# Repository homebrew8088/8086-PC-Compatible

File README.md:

# 8086 PC Compatible

This is a repository for my 8086 PC Compatible project developed in 2021. The Motherboard is built to be generally PC XT/AT compatible.\
\
THIS DOES NOT WORK CORRECTLY FOR REFERENCE ONLY  

https://www.homebrew8088.com \
http://www.ebay.com/sch/emil6190/m.html

**Features:**\
-8086, NEC V30\
-512k RAM (This can be changed)\
-16 Bit ISA Slots\
-PC Speaker\
-USB "Hard Drive"\
-PS/2 Keyboard\
-ATX form factor\
-Add on DMA controller (Has not been built) 

This project is very closely related to my other 8088 PC Compatible project https://github.com/homebrew8088/8088-PC-Compatible

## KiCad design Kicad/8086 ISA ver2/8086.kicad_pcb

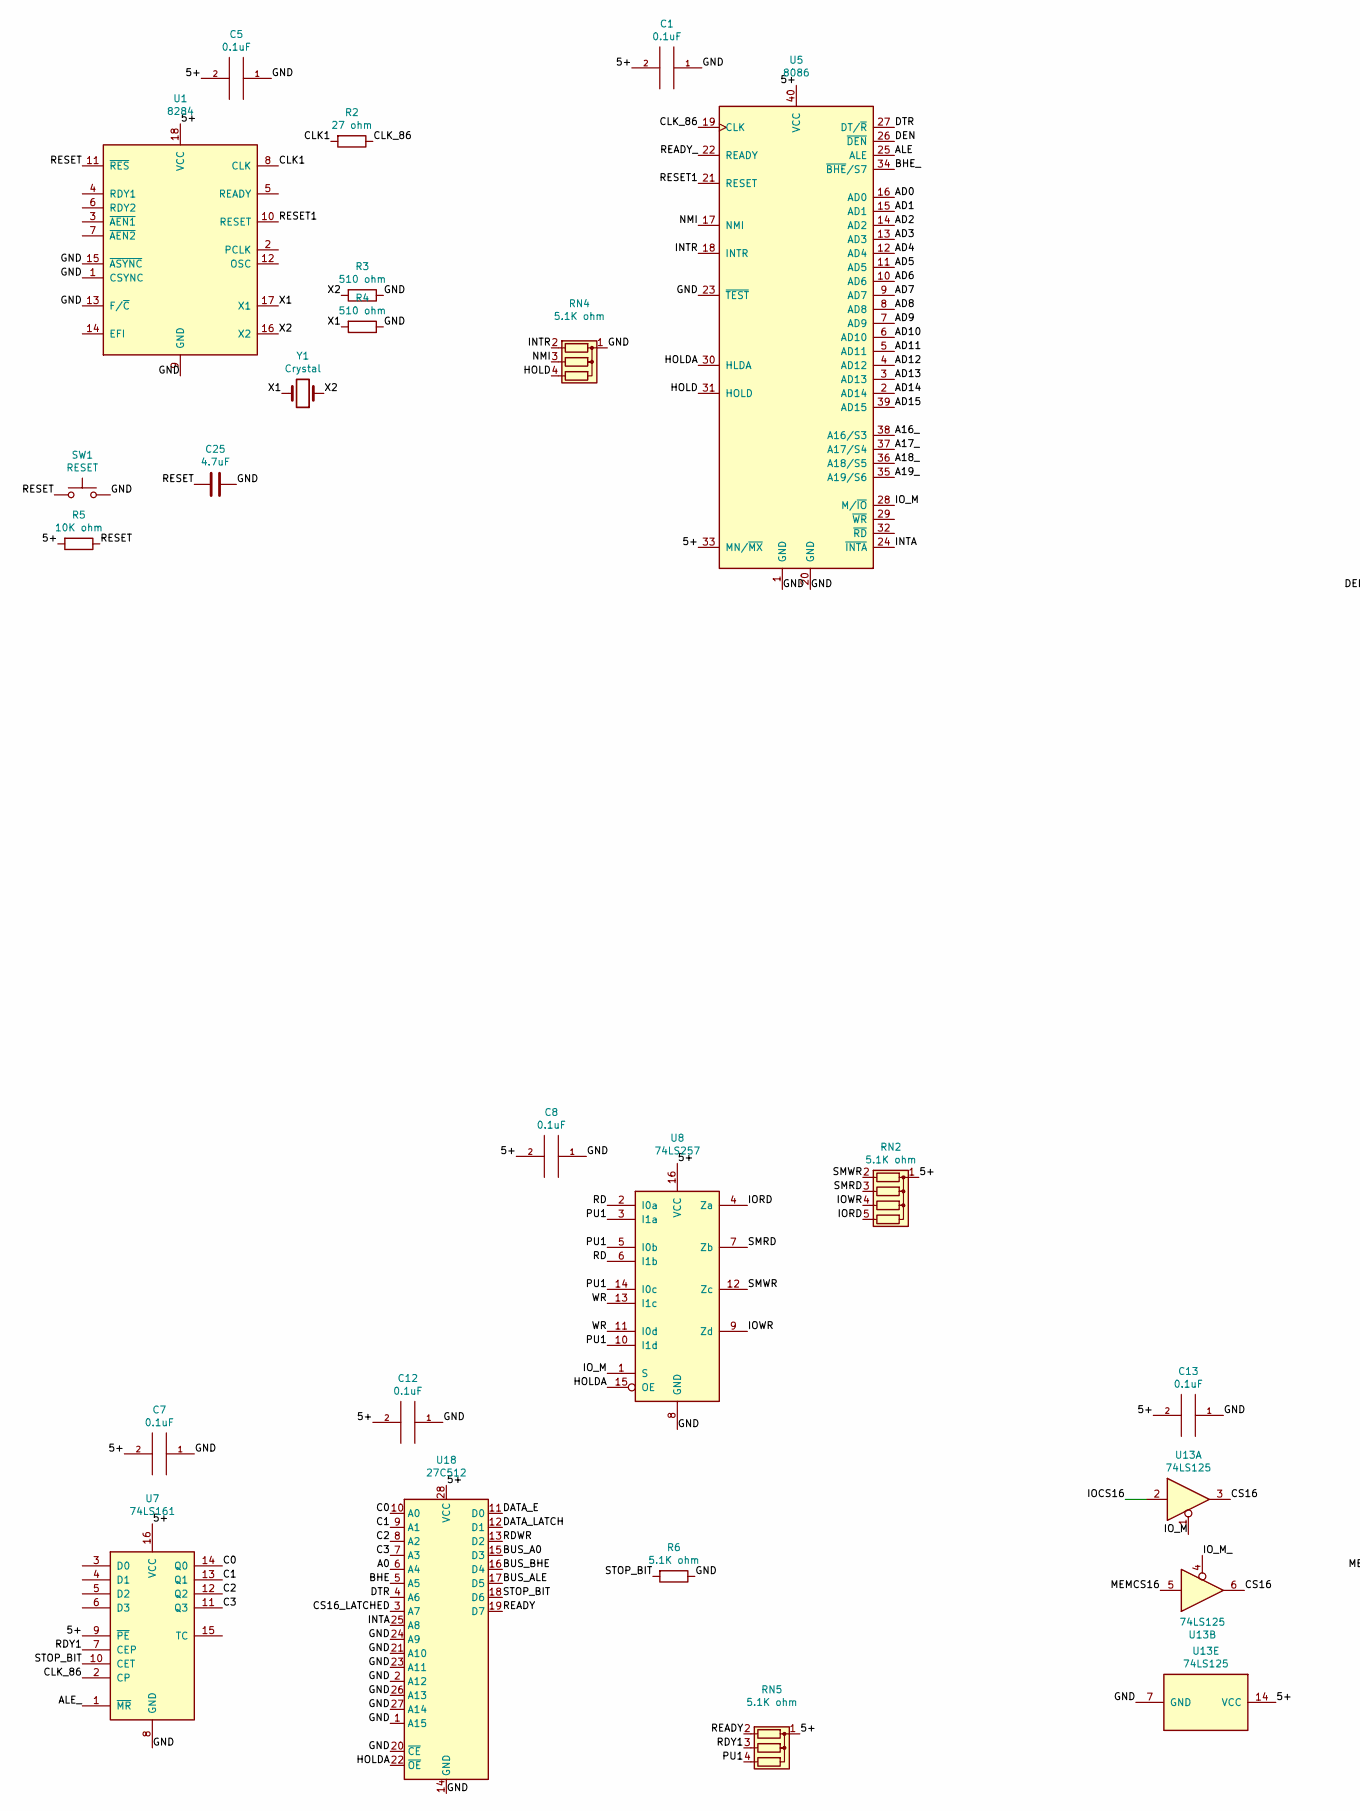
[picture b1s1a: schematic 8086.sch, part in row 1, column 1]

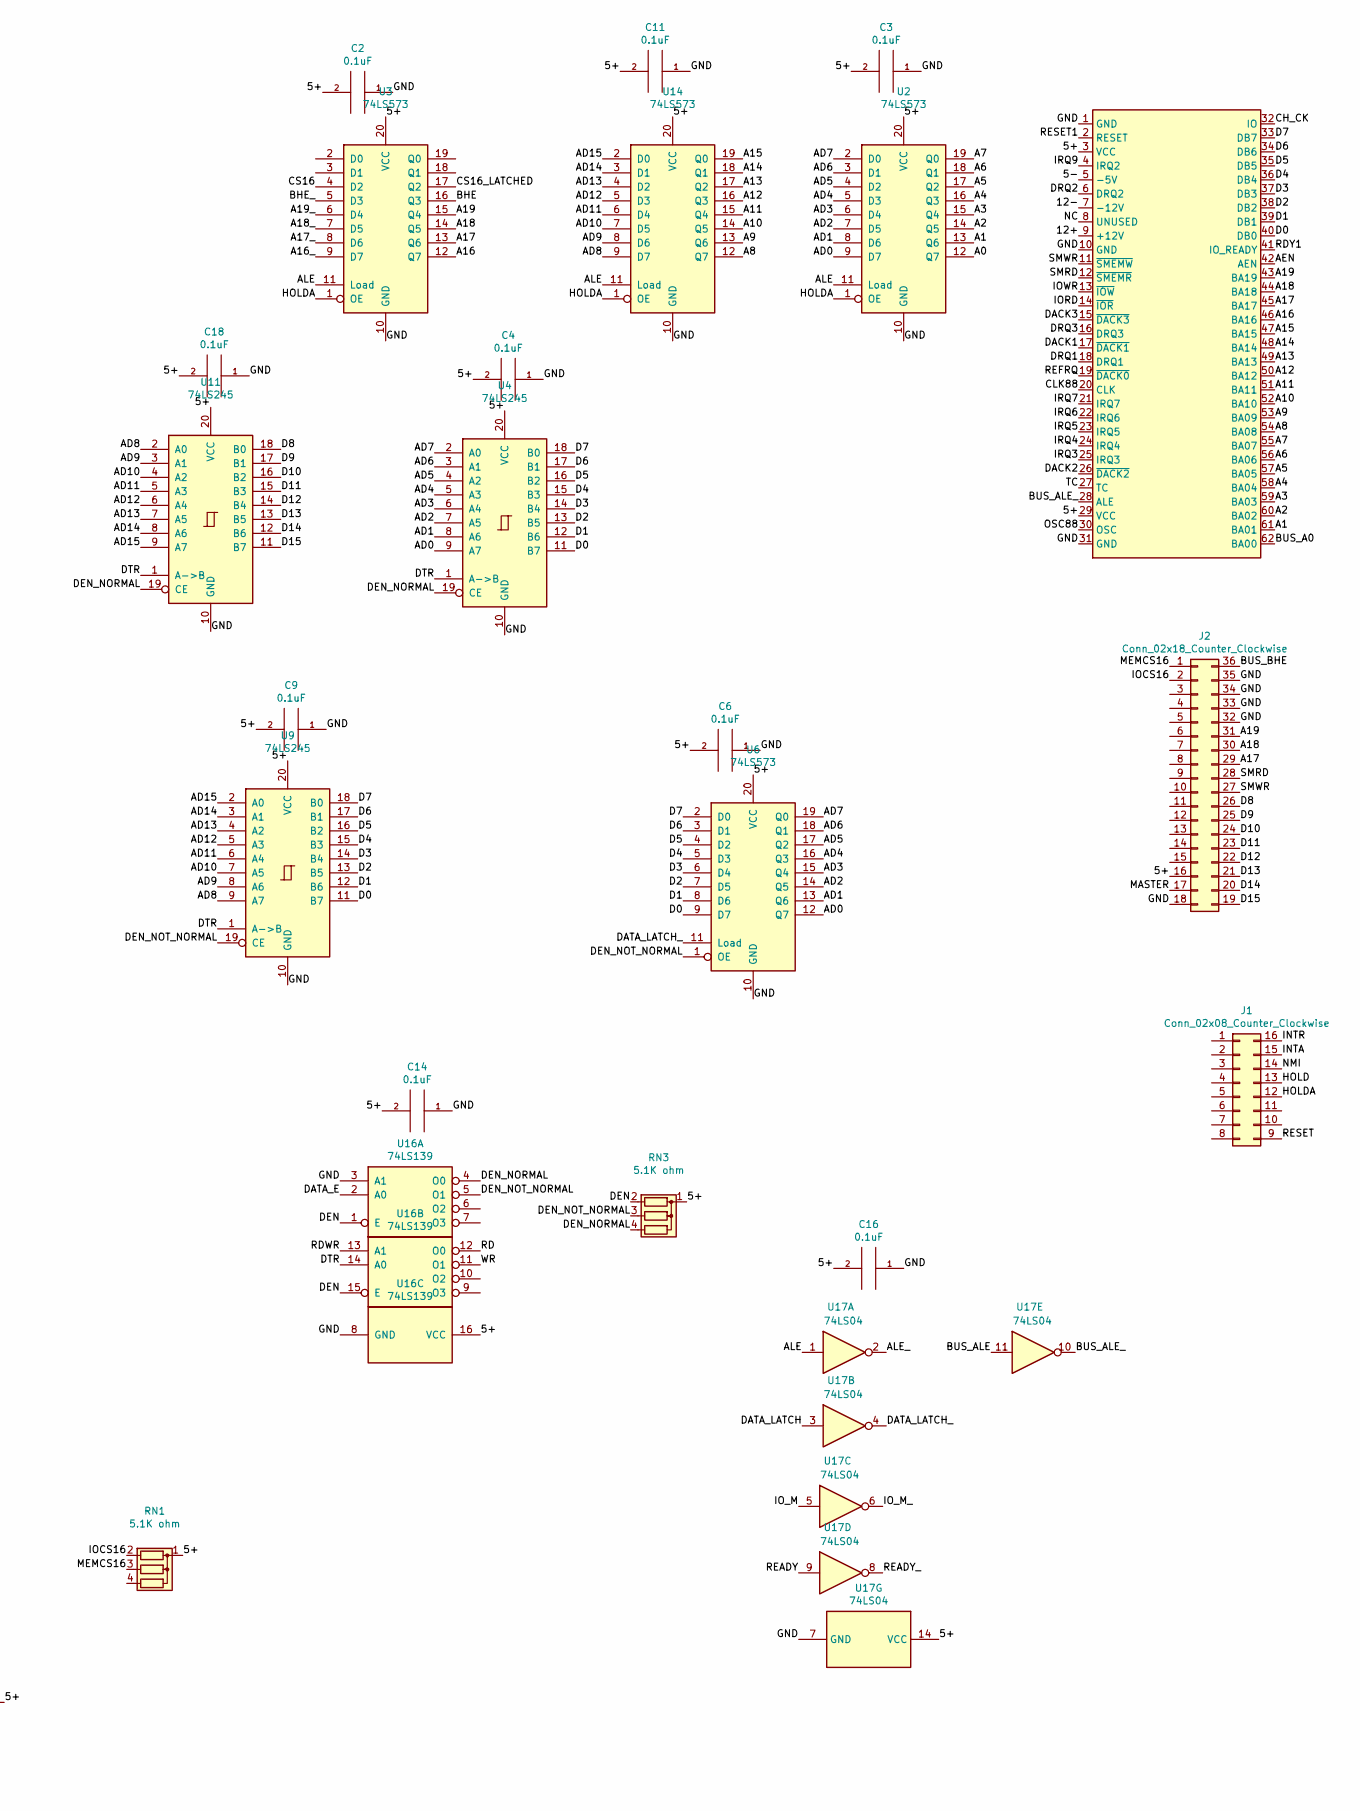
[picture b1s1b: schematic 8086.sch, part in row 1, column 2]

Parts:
C1, C2, C3, C4, C5, C6, C7, C8, C9, C11, C12, C13, C14, C16, C18: 0.1uF; C_Disc_D4.3mm_W1.9mm_P5.00mm
C25: 4.7uF; CP_Radial_D4.0mm_P1.50mm
J1: Conn_02x08_Counter_Clockwise; 16_EDGE_CARD_BUS
J2: Conn_02x18_Counter_Clockwise; 36_EDGE_CARD_BUS
J9: Bus_ISA_8bit; BUS_8_BIT
R2: 27 ohm; R_Axial_DIN0207_L6.3mm_D2.5mm_P10.16mm_Horizontal
R3, R4: 510 ohm; R_Axial_DIN0207_L6.3mm_D2.5mm_P10.16mm_Horizontal
R5: 10K ohm; R_Axial_DIN0207_L6.3mm_D2.5mm_P10.16mm_Horizontal
R6: 5.1K ohm; R_Axial_DIN0207_L6.3mm_D2.5mm_P10.16mm_Horizontal
RN1, RN3, RN4, RN5: 5.1K ohm; R_Array_SIP4
RN2: 5.1K ohm; R_Array_SIP5
SW1: RESET; SW_PUSH_6mm
U1: 8284; DIP-18_W7.62mm
U2, U3, U6, U14: 74LS573; DIP-20_W7.62mm
U4, U9, U11: 74LS245; DIP-20_W7.62mm
U5: 8086; DIP-40_W15.24mm
U7: 74LS161; DIP-16_W7.62mm
U8: 74LS257; DIP-16_W7.62mm
U13: 74LS125; DIP-14_W7.62mm
U16: 74LS139; DIP-16_W7.62mm
U17: 74LS04; DIP-14_W7.62mm
U18: 27C512; DIP-28_W15.24mm
Y1: Crystal; Crystal_HC18-U_Vertical

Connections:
/5+: C1.2, C2.2, C3.2, C4.2, C5.2, C6.2, C7.2, C8.2, C9.2, C11.2, C12.2, C13.2, C14.2, C16.2, C18.2, J2.16, J9.3 (VCC), J9.29 (VCC), R5.2, RN1.1 (common), RN2.1 (common), RN3.1 (common), RN5.1 (common), U1.18 (VCC), U2.20 (VCC), U3.20 (VCC), U4.20 (VCC), U5.33 (MN/~MX~), U5.40 (VCC), U6.20 (VCC), U7.9 (~PE), U7.16 (VCC), U8.16 (VCC), U9.20 (VCC), U11.20 (VCC), U13.14 (VCC), U14.20 (VCC), U16.16 (VCC), U17.14 (VCC), U18.28 (VCC)
/5-: J9.5 (-5V)
/12+: J9.9 (+12V)
/12-: J9.7 (-12V)
/A0: U2.12 (Q7), U18.6 (A4)
/A1: J9.61 (BA01), U2.13 (Q6)
/A2: J9.60 (BA02), U2.14 (Q5)
/A3: J9.59 (BA03), U2.15 (Q4)
/A4: J9.58 (BA04), U2.16 (Q3)
/A5: J9.57 (BA05), U2.17 (Q2)
/A6: J9.56 (BA06), U2.18 (Q1)
/A7: J9.55 (BA07), U2.19 (Q0)
/A8: J9.54 (BA08), U14.12 (Q7)
/A9: J9.53 (BA09), U14.13 (Q6)
/A10: J9.52 (BA10), U14.14 (Q5)
/A11: J9.51 (BA11), U14.15 (Q4)
/A12: J9.50 (BA12), U14.16 (Q3)
/A13: J9.49 (BA13), U14.17 (Q2)
/A14: J9.48 (BA14), U14.18 (Q1)
/A15: J9.47 (BA15), U14.19 (Q0)
/A16: J9.46 (BA16), U3.12 (Q7)
/A16_: U3.9 (D7), U5.38 (A16/S3)
/A17: J2.29, J9.45 (BA17), U3.13 (Q6)
/A17_: U3.8 (D6), U5.37 (A17/S4)
/A18: J2.30, J9.44 (BA18), U3.14 (Q5)
/A18_: U3.7 (D5), U5.36 (A18/S5)
/A19: J2.31, J9.43 (BA19), U3.15 (Q4)
/A19_: U3.6 (D4), U5.35 (A19/S6)
/AD0: U2.9 (D7), U4.9 (A7), U5.16 (AD0), U6.12 (Q7)
/AD1: U2.8 (D6), U4.8 (A6), U5.15 (AD1), U6.13 (Q6)
/AD2: U2.7 (D5), U4.7 (A5), U5.14 (AD2), U6.14 (Q5)
/AD3: U2.6 (D4), U4.6 (A4), U5.13 (AD3), U6.15 (Q4)
/AD4: U2.5 (D3), U4.5 (A3), U5.12 (AD4), U6.16 (Q3)
/AD5: U2.4 (D2), U4.4 (A2), U5.11 (AD5), U6.17 (Q2)
/AD6: U2.3 (D1), U4.3 (A1), U5.10 (AD6), U6.18 (Q1)
/AD7: U2.2 (D0), U4.2 (A0), U5.9 (AD7), U6.19 (Q0)
/AD8: U5.8 (AD8), U9.9 (A7), U11.2 (A0), U14.9 (D7)
/AD9: U5.7 (AD9), U9.8 (A6), U11.3 (A1), U14.8 (D6)
/AD10: U5.6 (AD10), U9.7 (A5), U11.4 (A2), U14.7 (D5)
/AD11: U5.5 (AD11), U9.6 (A4), U11.5 (A3), U14.6 (D4)
/AD12: U5.4 (AD12), U9.5 (A3), U11.6 (A4), U14.5 (D3)
/AD13: U5.3 (AD13), U9.4 (A2), U11.7 (A5), U14.4 (D2)
/AD14: U5.2 (AD14), U9.3 (A1), U11.8 (A6), U14.3 (D1)
/AD15: U5.39 (AD15), U9.2 (A0), U11.9 (A7), U14.2 (D0)
/AEN: J9.42 (AEN)
/ALE: U2.11 (Load), U3.11 (Load), U5.25 (ALE), U14.11 (Load), U17.1
/ALE_: U7.1 (~MR), U17.2
/BHE: U3.16 (Q3), U18.5 (A5)
/BHE_: U3.5 (D3), U5.34 (~BHE~/S7)
/BUS_A0: J9.62 (BA00), U18.15 (D3)
/BUS_ALE: U17.11, U18.17 (D5)
/BUS_ALE_: J9.28 (ALE), U17.10
/BUS_BHE: J2.36, U18.16 (D4)
/C0: U7.14 (Q0), U18.10 (A0)
/C1: U7.13 (Q1), U18.9 (A1)
/C2: U7.12 (Q2), U18.8 (A2)
/C3: U7.11 (Q3), U18.7 (A3)
/CH_CK: J9.32 (IO)
/CLK1: R2.2, U1.8 (CLK)
/CLK88: J9.20 (CLK)
/CLK_86: R2.1, U5.19 (CLK), U7.2 (CP)
/CS16: U3.4 (D2), U13.3, U13.6
/CS16_LATCHED: U3.17 (Q2), U18.3 (A7)
/D0: J9.40 (DB0), U4.11 (B7), U6.9 (D7), U9.11 (B7)
/D1: J9.39 (DB1), U4.12 (B6), U6.8 (D6), U9.12 (B6)
/D2: J9.38 (DB2), U4.13 (B5), U6.7 (D5), U9.13 (B5)
/D3: J9.37 (DB3), U4.14 (B4), U6.6 (D4), U9.14 (B4)
/D4: J9.36 (DB4), U4.15 (B3), U6.5 (D3), U9.15 (B3)
/D5: J9.35 (DB5), U4.16 (B2), U6.4 (D2), U9.16 (B2)
/D6: J9.34 (DB6), U4.17 (B1), U6.3 (D1), U9.17 (B1)
/D7: J9.33 (DB7), U4.18 (B0), U6.2 (D0), U9.18 (B0)
/D8: J2.26, U11.18 (B0)
/D9: J2.25, U11.17 (B1)
/D10: J2.24, U11.16 (B2)
/D11: J2.23, U11.15 (B3)
/D12: J2.22, U11.14 (B4)
/D13: J2.21, U11.13 (B5)
/D14: J2.20, U11.12 (B6)
/D15: J2.19, U11.11 (B7)
/DACK1: J9.17 (~DACK1)
/DACK2: J9.26 (~DACK2)
/DACK3: J9.15 (~DACK3)
/DATA_E: U16.2 (A0), U18.11 (D0)
/DATA_LATCH: U17.3, U18.12 (D1)
/DATA_LATCH_: U6.11 (Load), U17.4
/DEN: RN3.2 (R1), U5.26 (~DEN~), U16.1 (E), U16.15 (E)
/DEN_NORMAL: RN3.4 (R3), U4.19 (CE), U11.19 (CE), U16.4 (O0)
/DEN_NOT_NORMAL: RN3.3 (R2), U6.1 (OE), U9.19 (CE), U16.5 (O1)
/DRQ1: J9.18 (DRQ1)
/DRQ2: J9.6 (DRQ2)
/DRQ3: J9.16 (DRQ3)
/DTR: U4.1 (A->B), U5.27 (DT/~R~), U9.1 (A->B), U11.1 (A->B), U16.14 (A0), U18.4 (A6)
/GND: C1.1, C2.1, C3.1, C4.1, C5.1, C6.1, C7.1, C8.1, C9.1, C11.1, C12.1, C13.1, C14.1, C16.1, C18.1, C25.2, J2.18, J2.32, J2.33, J2.34, J2.35, J9.1 (GND), J9.10 (GND), J9.31 (GND), R3.1, R4.1, R6.1, RN4.1 (common), SW1.2, U1.1 (CSYNC), U1.9 (GND), U1.13 (F/~C~), U1.15 (~ASYNC~), U2.10 (GND), U3.10 (GND), U4.10 (GND), U5.1 (GND), U5.20 (GND), U5.23 (~TEST~), U6.10 (GND), U7.8 (GND), U8.8 (GND), U9.10 (GND), U11.10 (GND), U13.7 (GND), U14.10 (GND), U16.3 (A1), U16.8 (GND), U17.7 (GND), U18.1 (A15), U18.2 (A12), U18.14 (GND), U18.20 (~CE), U18.21 (A10), U18.23 (A11), U18.24 (A9), U18.26 (A13), U18.27 (A14); also elsewhere on the board
/HOLD: J1.13, RN4.4 (R3), U5.31 (HOLD)
/HOLDA: J1.12, U2.1 (OE), U3.1 (OE), U5.30 (HLDA), U8.15 (OE), U14.1 (OE), U18.22 (~OE)
/INTA: J1.15, U5.24 (~INTA~), U18.25 (A8)
/INTR: J1.16, RN4.2 (R1), U5.18 (INTR)
/IOCS16: J2.2, RN1.2 (R1), U13.2
/IORD: J9.14 (~IOR), RN2.5 (R4), U8.4 (Za)
/IOWR: J9.13 (~IOW), RN2.4 (R3), U8.9 (Zd)
/IO_M: U5.28 (M/~IO~), U8.1 (S), U13.1, U17.5
/IO_M_: U13.4, U17.6
/IRQ3: J9.25 (IRQ3)
/IRQ4: J9.24 (IRQ4)
/IRQ5: J9.23 (IRQ5)
/IRQ6: J9.22 (IRQ6)
/IRQ7: J9.21 (IRQ7)
/IRQ9: J9.4 (IRQ2)
/MASTER: J2.17
/MEMCS16: J2.1, RN1.3 (R2), U13.5
/NC: J9.8 (UNUSED)
/NMI: J1.14, RN4.3 (R2), U5.17 (NMI)
/OSC88: J9.30 (OSC)
/PU1: RN5.4 (R3), U8.3 (I1a), U8.5 (I0b), U8.10 (I1d), U8.14 (I0c)
/RD: U8.2 (I0a), U8.6 (I1b), U16.12 (O0)
/RDWR: U16.13 (A1), U18.13 (D2)
/RDY1: J9.41 (IO_READY), RN5.3 (R2), U7.7 (CEP)
/READY: RN5.2 (R1), U17.9, U18.19 (D7)
/READY_: U5.22 (READY), U17.8
/REFRQ: J9.19 (~DACK0)
/RESET: C25.1, J1.9, R5.1, SW1.1, U1.11 (~RES~)
/RESET1: J9.2 (RESET), U1.10 (RESET), U5.21 (RESET)
/SMRD: J2.28, J9.12 (~SMEMR), RN2.3 (R2), U8.7 (Zb)
/SMWR: J2.27, J9.11 (~SMEMW), RN2.2 (R1), U8.12 (Zc)
/STOP_BIT: R6.2, U7.10 (CET), U18.18 (D6)
/TC: J9.27 (TC)
/WR: U8.11 (I0d), U8.13 (I1c), U16.11 (O1)
/X1: R4.2, U1.17 (X1), Y1.2
/X2: R3.2, U1.16 (X2), Y1.1

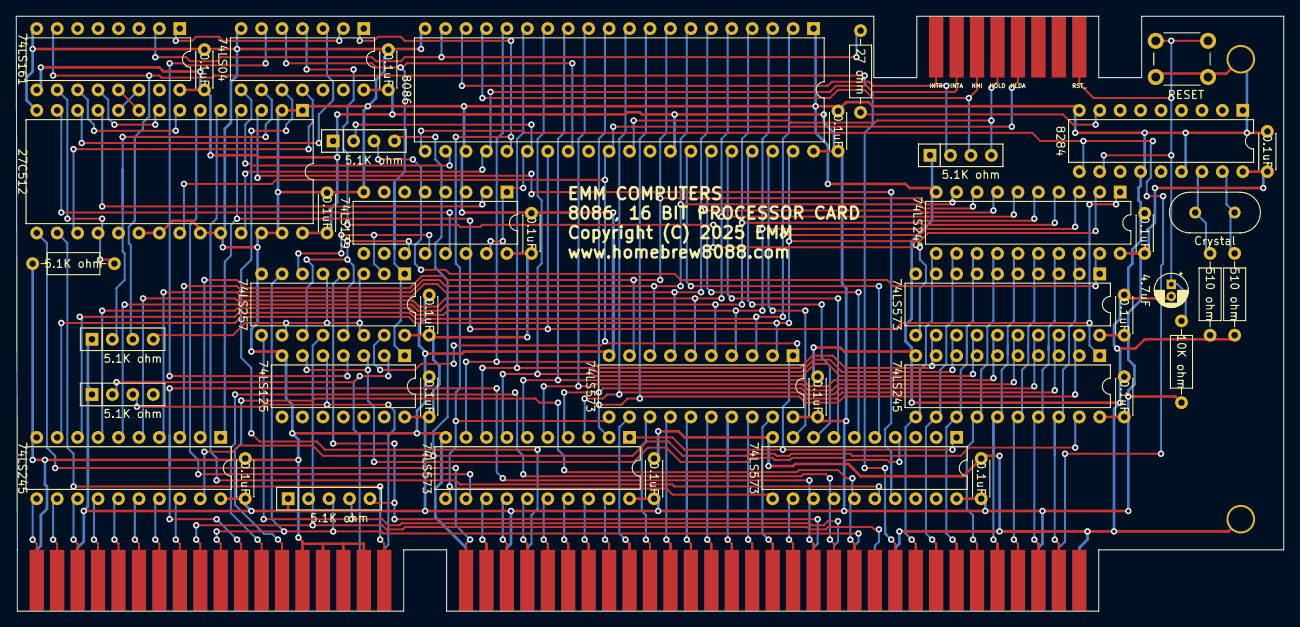
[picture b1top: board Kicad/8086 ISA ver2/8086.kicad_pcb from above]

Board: 2 copper layers, 157.5 x 73.9 mm, 48 parts (0 on the bottom side), 106 nets.

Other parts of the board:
R: L; Large_Via
R#2: L; Large_Via

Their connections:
/GND: R.1, R#2.1; also elsewhere on the board

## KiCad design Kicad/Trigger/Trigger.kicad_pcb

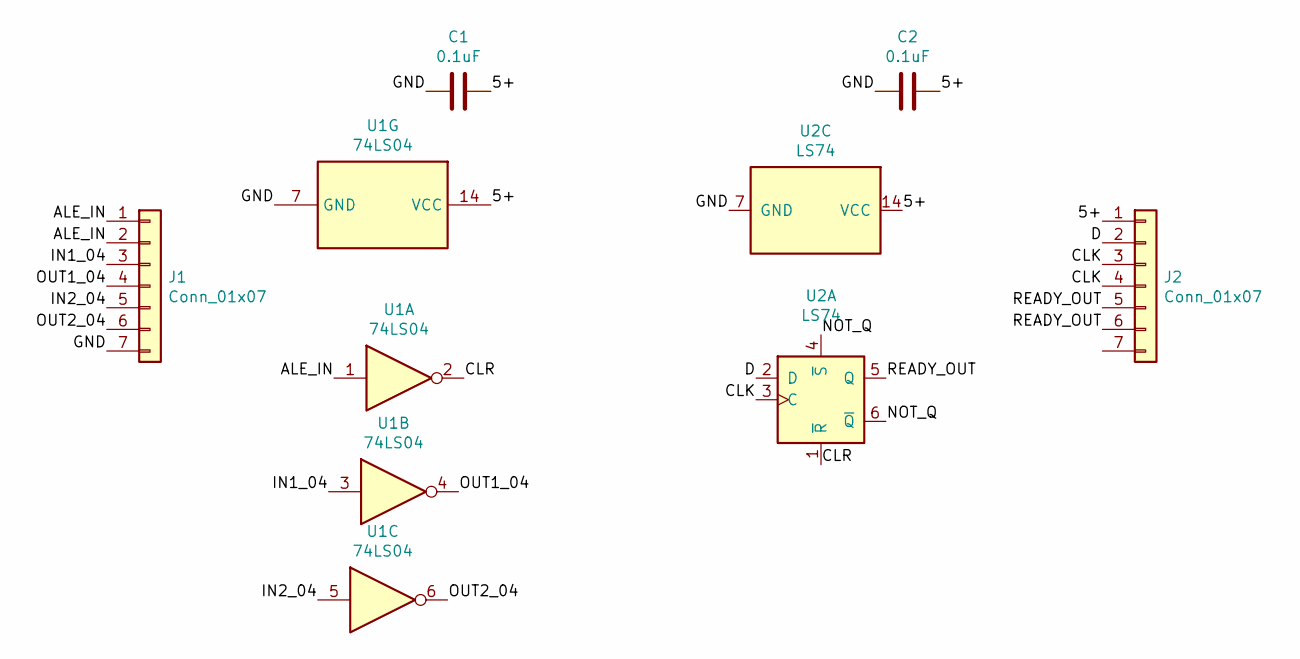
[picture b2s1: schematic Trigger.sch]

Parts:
C1, C2: 0.1uF; C_Disc_D4.3mm_W1.9mm_P5.00mm
J1, J2: Conn_01x07; PinHeader_1x07_P2.54mm_Vertical
U1: 74LS04; DIP-14_W7.62mm
U2: LS74; DIP-14_W7.62mm

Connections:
/5+: C1.1, C2.1, J2.1, U1.14 (VCC), U2.14 (VCC)
/ALE_IN: J1.1, J1.2, U1.1
/CLK: J2.3, J2.4, U2.3 (C)
/CLR: U1.2, U2.1 (~R)
/D: J2.2, U2.2 (D)
/GND: C1.2, C2.2, J1.7, U1.7 (GND), U2.7 (GND)
/IN1_04: J1.3, U1.3
/IN2_04: J1.5, U1.5
/NOT_Q: U2.4 (~S), U2.6 (~Q)
/OUT1_04: J1.4, U1.4
/OUT2_04: J1.6, U1.6
/READY_OUT: J2.5, J2.6, U2.5 (Q)

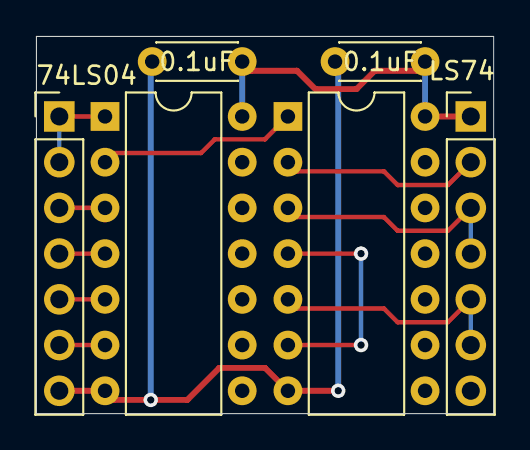
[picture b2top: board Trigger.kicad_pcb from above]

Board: 2 copper layers, 25.4 x 21.0 mm, 6 parts (0 on the bottom side), 12 nets.

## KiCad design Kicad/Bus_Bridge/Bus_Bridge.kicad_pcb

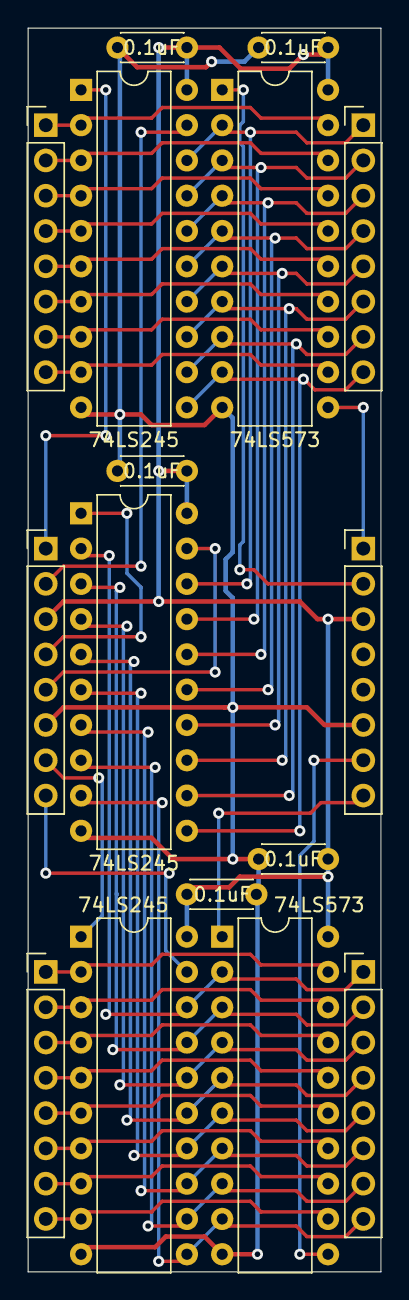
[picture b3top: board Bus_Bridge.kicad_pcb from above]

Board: 2 copper layers, 25.4 x 89.5 mm, 16 parts (0 on the bottom side), 44 nets.

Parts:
C1, C2, C3, C4, C5: 0.1uF; C_Disc_D4.3mm_W1.9mm_P5.00mm
J1, J2, J3, J4, J5, J6: Conn_01x08; PinHeader_1x08_P2.54mm_Vertical
U1, U2, U3: 74LS245; DIP-20_W7.62mm
U4, U5: 74LS573; DIP-20_W7.62mm

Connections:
/0_7_245_DIR: J3.1, U1.1
/0_7_245_E: J3.2, U1.19
/0_7_573_E: J5.2, U5.1
/0_7_573_LATCH: J5.1, U5.11
/5+: C1.1, C2.1, C3.1, C4.1, C5.1, J3.3, J5.3, U1.20, U2.20, U3.20, U4.20, U5.20
/8_15_245_DIR: J3.7, U2.1
/8_15_245_E: J3.8, U2.19
/8_15_573_E: J5.8, U4.1
/8_15_573_LATCH: J5.7, U4.11
/BRIDGE_DIR: J3.4, U3.1
/BRIDGE_E: J3.5, U3.19
/BUS_D0: J6.1, U1.18, U3.18, U5.2
/BUS_D1: J6.2, U1.17, U3.17, U5.3
/BUS_D2: J6.3, U1.16, U3.16, U5.4
/BUS_D3: J6.4, U1.15, U3.15, U5.5
/BUS_D4: J6.5, U1.14, U3.14, U5.6
/BUS_D5: J6.6, U1.13, U3.13, U5.7
/BUS_D6: J6.7, U1.12, U3.12, U5.8
/BUS_D7: J6.8, U1.11, U3.11, U5.9
/BUS_D8: J4.1, U2.18, U3.2, U4.2
/BUS_D9: J4.2, U2.17, U3.3, U4.3
/BUS_D10: J4.3, U2.16, U3.4, U4.4
/BUS_D11: J4.4, U2.15, U3.5, U4.5
/BUS_D12: J4.5, U2.14, U3.6, U4.6
/BUS_D13: J4.6, U2.13, U3.7, U4.7
/BUS_D14: J4.7, U2.12, U3.8, U4.8
/BUS_D15: J4.8, U2.11, U3.9, U4.9
/CPU_D0: J1.1, U1.2, U5.19
/CPU_D1: J1.2, U1.3, U5.18
/CPU_D2: J1.3, U1.4, U5.17
/CPU_D3: J1.4, U1.5, U5.16
/CPU_D4: J1.5, U1.6, U5.15
/CPU_D5: J1.6, U1.7, U5.14
/CPU_D6: J1.7, U1.8, U5.13
/CPU_D7: J1.8, U1.9, U5.12
/CPU_D8: J2.1, U2.2, U4.19
/CPU_D9: J2.2, U2.3, U4.18
/CPU_D10: J2.3, U2.4, U4.17
/CPU_D11: J2.4, U2.5, U4.16
/CPU_D12: J2.5, U2.6, U4.15
/CPU_D13: J2.6, U2.7, U4.14
/CPU_D14: J2.7, U2.8, U4.13
/CPU_D15: J2.8, U2.9, U4.12
/GND: C1.2, C2.2, C3.2, C4.2, C5.2, J3.6, J5.6, U1.10, U2.10, U3.10, U4.10, U5.10

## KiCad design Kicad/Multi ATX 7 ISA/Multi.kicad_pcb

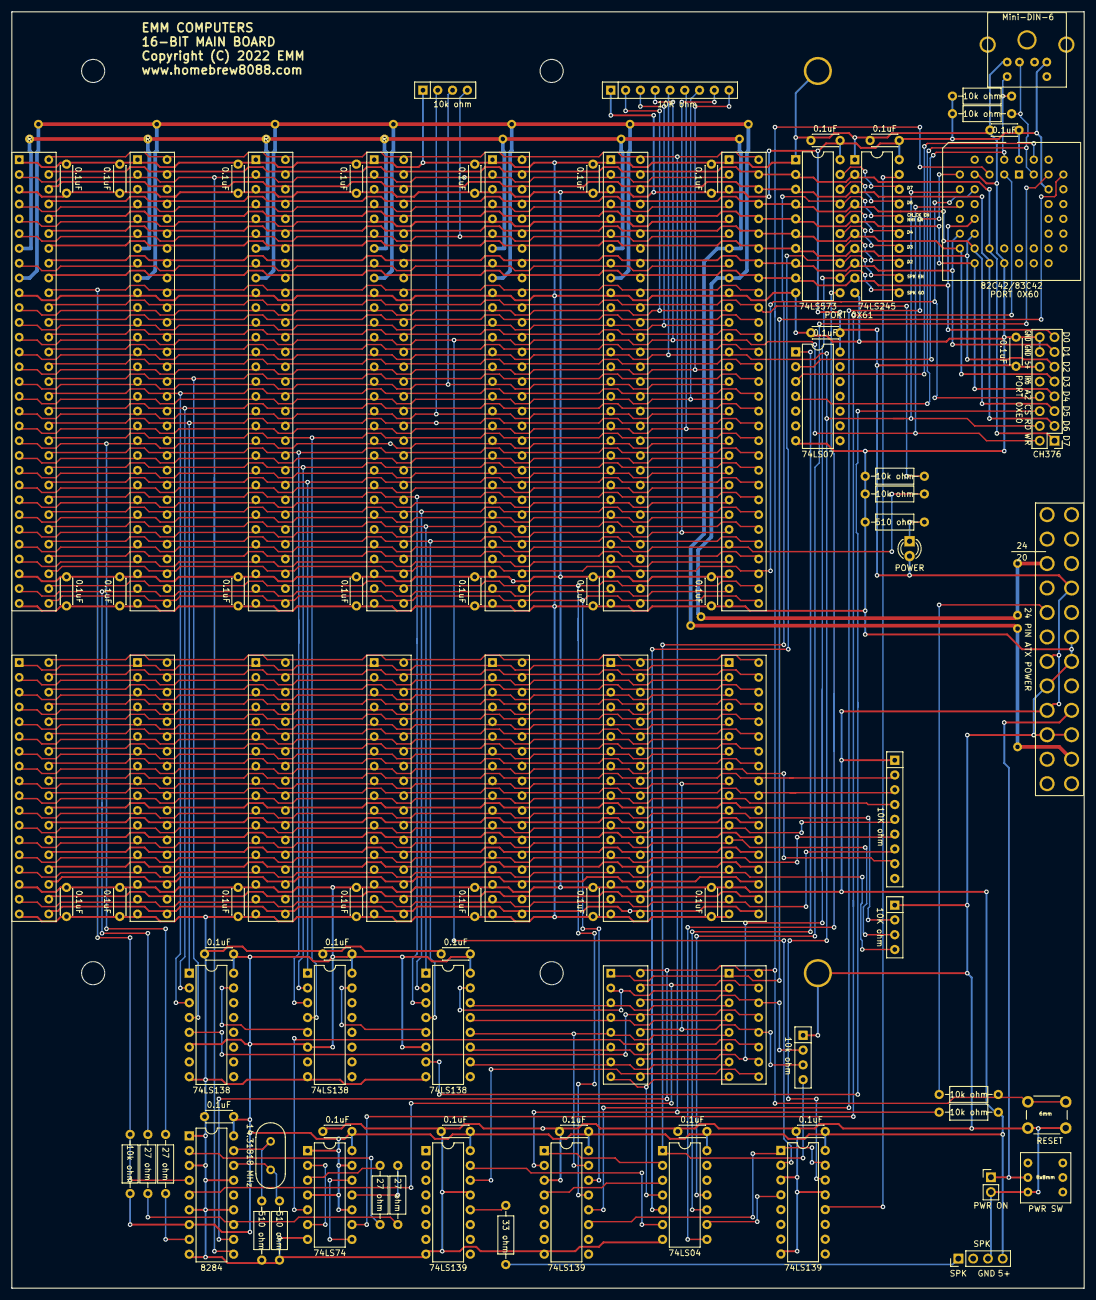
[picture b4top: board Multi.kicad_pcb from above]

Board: 2 copper layers, 184.2 x 219.2 mm, 113 parts (0 on the bottom side), 146 nets.

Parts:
8x8mm1: PWR SW; 6 PIN DTDP
ATXPOWER1: Conn_02x12_Top_Bottom; 24_PIN_ATX_POWER
C1, C1#2, C2, C3, C4, C5, C6, C7, C8, C9, C10, C11, C12, C13, C14, C15, C16, C17, C18, C19, C20, C21, C22, C23, C24, C25, C26, C27, C28, C29, C30, C31, C32, C33, C34: 0.1uF; C_Disc_D4.3mm_W1.9mm_P5.00mm
CH376: PORT 0XE0; PinHeader_2x08_P2.54mm_Vertical
D1: POWER; LED_D3.0mm
J1, J7, J8, J9, J12, J13, J14: Bus_ISA_8bit; 8-bit-ISA
J2: Mini-DIN-6; 6_PIN_DIN
J3: SPK; PinHeader_1x04_P2.54mm_Vertical
J4, J15, J16, J17, J18, J19, J20: Conn_02x18_Counter_Clockwise; 2x18_PIN_EDGE_CARD
J6: PWR ON; PinHeader_1x02_P2.54mm_Vertical
J10, J11: Conn_02x08_Counter_Clockwise; 2x08_PIN_EDGE_CARD
R: L; Large_Via
R1, R2, R4: 510 ohm; R_Axial_DIN0207_L6.3mm_D2.5mm_P10.16mm_Horizontal
R3, R14, R17, R18: 27 ohm; R_Axial_DIN0207_L6.3mm_D2.5mm_P10.16mm_Horizontal
R5, R6, R7, R8, R9, R12, R13: 10k ohm; R_Axial_DIN0207_L6.3mm_D2.5mm_P10.16mm_Horizontal
R#2, R#3, R#4, R#5, R#6, R#7, R#8, R#9, R#10, R#11, R#12, R#13, R#14, R#15, R#16, R#17, R#18, R#19, R#20: L; Large_Via
RN1, RN3: 10k ohm; R_Array_SIP4
RN2, RN5: 10K ohm; R_Array_SIP9
RN4: 10K ohm; R_Array_SIP4
SW1: RESET; SW_PUSH_6mm
U1, U17, U117: 74LS139; DIP-16_W7.62mm
U2: 74LS245; DIP-20_W7.62mm
U3: 33 ohm; R_Axial_DIN0207_L6.3mm_D2.5mm_P10.16mm_Horizontal
U9, U12, U13: 74LS138; DIP-16_W7.62mm
U11: 8284; DIP-18_W7.62mm
U14: 74LS74; DIP-14_W7.62mm
U15: 74LS573; DIP-20_W7.62mm
U16: 74LS04; DIP-14_W7.62mm
U19: 82C42/83C42; PLCC-44_THT-Socket
U20: 74LS07; DIP-14_W7.62mm
Y2: 14.31818 MHz; Crystal_HC18-U_Vertical

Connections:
/5+: ATXPOWER1.4, ATXPOWER1.6, ATXPOWER1.21, C1.2, C1#2.2, C2.2, C3.2, C4.2, C5.2, C6.2, C7.2, C8.2, C9.2, C10.2, C11.2, C12.2, C13.2, C14.2, C15.2, C16.2, C17.2, C18.2, C19.2, C20.2, C21.2, C22.2, C23.2, C24.2, C25.2, C26.2, C27.2, C28.2, C29.2, C30.2, C31.2, C32.2, C33.2, C34.2, CH376.12, D1.2, J1.3, J1.29, J2.4, J3.4, J4.16, J7.3, J7.29, J8.3, J8.29, J9.3, J9.29, J12.3, J12.29, J13.3, J13.29, J14.3, J14.29, J15.16, J16.16, J17.16, J18.16, J19.16, J20.16, R6.1, R7.1, R8.1, R9.1, RN2.1, RN5.1, U1.16, U2.20, U9.6, U9.16, U11.7, U11.18, U12.6, U12.16, U13.6, U13.16, U14.1, U14.4, U14.10, U14.13, U14.14, U15.20, U16.14, U17.16, U19.38, U19.44, U20.14, U117.16
/5-: J1.5, J7.5, J8.5, J9.5, J12.5, J13.5, J14.5
/12+: ATXPOWER1.10, J1.9, J7.9, J8.9, J9.9, J12.9, J13.9, J14.9, R.1, R#3.1, R#5.1, R#7.1, R#8.1, R#12.1, R#14.1, R#15.1, R#18.1, R#20.1
/12-: ATXPOWER1.14, J1.7, J7.7, J8.7, J9.7, J12.7, J13.7, J14.7, R#2.1, R#4.1, R#6.1, R#9.1, R#10.1, R#11.1, R#13.1, R#16.1, R#17.1, R#19.1
/A0: J1.62, J7.62, J8.62, J9.62, J12.62, J13.62, J14.62, U17.14
/A1: J1.61, J7.61, J8.61, J9.61, J12.61, J13.61, J14.61, U17.13
/A2: CH376.8, J1.60, J7.60, J8.60, J9.60, J12.60, J13.60, J14.60, U19.10
/A3: J1.59, J7.59, J8.59, J9.59, J12.59, J13.59, J14.59
/A4: J1.58, J7.58, J8.58, J9.58, J12.58, J13.58, J14.58, U13.4
/A5: J1.57, J7.57, J8.57, J9.57, J12.57, J13.57, J14.57, U13.1
/A6: J1.56, J7.56, J8.56, J9.56, J12.56, J13.56, J14.56, U13.2
/A7: J1.55, J7.55, J8.55, J9.55, J12.55, J13.55, J14.55, U13.3
/A8: J1.54, J7.54, J8.54, J9.54, J12.54, J13.54, J14.54, U12.1
/A9: J1.53, J7.53, J8.53, J9.53, J12.53, J13.53, J14.53, U12.2
/A10: J1.52, J7.52, J8.52, J9.52, J12.52, J13.52, J14.52, U12.3
/A11: J1.51, J7.51, J8.51, J9.51, J12.51, J13.51, J14.51, U12.4
/A12: J1.50, J7.50, J8.50, J9.50, J12.50, J13.50, J14.50, U9.1
/A13: J1.49, J7.49, J8.49, J9.49, J12.49, J13.49, J14.49, U9.2
/A14: J1.48, J7.48, J8.48, J9.48, J12.48, J13.48, J14.48, U9.3
/A15: J1.47, J7.47, J8.47, J9.47, J12.47, J13.47, J14.47, U9.4
/A16: J1.46, J7.46, J8.46, J9.46, J12.46, J13.46, J14.46
/A17: J1.45, J7.45, J8.45, J9.45, J12.45, J13.45, J14.45
/A18: J1.44, J7.44, J8.44, J9.44, J12.44, J13.44, J14.44
/A19: J1.43, J7.43, J8.43, J9.43, J12.43, J13.43, J14.43
/AEN: J1.42, J7.42, J8.42, J9.42, J12.42, J13.42, J14.42, R12.2
/ALE: J1.28, J7.28, J8.28, J9.28, J12.28, J13.28, J14.28
/CH_CK: J1.32, J7.32, J8.32, J9.32, J12.32, J13.32, J14.32, R7.2, U17.2
/CLK: R18.2, U11.8
/CLK88: J1.20, J7.20, J8.20, J9.20, J12.20, J13.20, J14.20, R18.1
/D0: CH376.15, J1.40, J7.40, J8.40, J9.40, J12.40, J13.40, J14.40, U2.9, U15.9, U19.14
/D1: CH376.13, J1.39, J7.39, J8.39, J9.39, J12.39, J13.39, J14.39, U2.8, U15.8, U19.15
/D2: CH376.11, J1.38, J7.38, J8.38, J9.38, J12.38, J13.38, J14.38, U2.7, U15.7, U19.16
/D3: CH376.9, J1.37, J7.37, J8.37, J9.37, J12.37, J13.37, J14.37, U2.6, U15.6, U19.17
/D4: CH376.7, J1.36, J7.36, J8.36, J9.36, J12.36, J13.36, J14.36, U2.5, U15.5, U19.18
/D5: CH376.5, J1.35, J7.35, J8.35, J9.35, J12.35, J13.35, J14.35, U2.4, U15.4, U19.19
/D6: CH376.3, J1.34, J7.34, J8.34, J9.34, J12.34, J13.34, J14.34, U2.3, U15.3, U19.20
/D7: CH376.1, J1.33, J7.33, J8.33, J9.33, J12.33, J13.33, J14.33, U2.2, U15.2, U19.21
/D8: J4.26, J15.26, J16.26, J17.26, J18.26, J19.26, J20.26
/D9: J4.25, J15.25, J16.25, J17.25, J18.25, J19.25, J20.25
/D10: J4.24, J15.24, J16.24, J17.24, J18.24, J19.24, J20.24
/D11: J4.23, J15.23, J16.23, J17.23, J18.23, J19.23, J20.23
/D12: J4.22, J15.22, J16.22, J17.22, J18.22, J19.22, J20.22
/D13: J4.21, J15.21, J16.21, J17.21, J18.21, J19.21, J20.21
/D14: J4.20, J15.20, J16.20, J17.20, J18.20, J19.20, J20.20
/D15: J4.19, J15.19, J16.19, J17.19, J18.19, J19.19, J20.19
/DACK0: J4.8, J15.8, J16.8, J17.8, J18.8, J19.8, J20.8, RN5.8
/DACK1: J1.17, J7.17, J8.17, J9.17, J12.17, J13.17, J14.17, RN2.7
/DACK2: J1.26, J7.26, J8.26, J9.26, J12.26, J13.26, J14.26, RN2.8
/DACK3: J1.15, J7.15, J8.15, J9.15, J12.15, J13.15, J14.15, RN2.9
/DACK5: J4.10, J15.10, J16.10, J17.10, J18.10, J19.10, J20.10, RN5.4
/DACK6: J4.12, J15.12, J16.12, J17.12, J18.12, J19.12, J20.12, RN5.5
/DACK7: J4.14, J15.14, J16.14, J17.14, J18.14, J19.14, J20.14, RN5.6
/DRQ0: J4.9, J10.12, J11.12, J15.9, J16.9, J17.9, J18.9, J19.9, J20.9, RN3.3
/DRQ1: J1.18, J7.18, J8.18, J9.18, J12.18, J13.18, J14.18, RN1.2
/DRQ2: J1.6, J7.6, J8.6, J9.6, J12.6, J13.6, J14.6, RN1.4
/DRQ3: J1.16, J7.16, J8.16, J9.16, J12.16, J13.16, J14.16, RN1.3
/DRQ5: J4.11, J15.11, J16.11, J17.11, J18.11, J19.11, J20.11, RN4.2
/DRQ6: J4.13, J15.13, J16.13, J17.13, J18.13, J19.13, J20.13, RN4.3
/DRQ7: J4.15, J15.15, J16.15, J17.15, J18.15, J19.15, J20.15, RN4.4
/FB1: U14.8, U14.12
/FB2: U14.2, U14.6
/GND: 8x8mm1.3, ATXPOWER1.3, ATXPOWER1.5, ATXPOWER1.15, ATXPOWER1.18, ATXPOWER1.19, C1.1, C1#2.1, C2.1, C3.1, C4.1, C5.1, C6.1, C7.1, C8.1, C9.1, C10.1, C11.1, C12.1, C13.1, C14.1, C15.1, C16.1, C17.1, C18.1, C19.1, C20.1, C21.1, C22.1, C23.1, C24.1, C25.1, C26.1, C27.1, C28.1, C29.1, C30.1, C31.1, C32.1, C33.1, C34.1, CH376.14, CH376.16, J1.1, J1.10, J1.31, J2.3, J3.3, J4.18, J6.2, J7.1, J7.10, J7.31, J8.1, J8.10, J8.31, J9.1, J9.10, J9.31, J12.1, J12.10, J12.31, J13.1, J13.10, J13.31, J14.1, J14.10, J14.31, J15.18, J16.18, J17.18, J18.18, J19.18, J20.18, R1.2, R2.2, R4.2, R12.1, R13.1, RN1.1, RN3.1, RN4.1, SW1.2, U1.3, U1.8, U1.13, U2.1, U2.10, U9.8, U11.1, U11.3, U11.6, U11.9, U11.13, U11.15, U12.8, U13.8, U14.7, U15.1, U15.10, U16.7, U17.3, U17.8, U19.8, U19.22, U20.7, U117.8, U117.13
/HF_OSC: U14.9, U19.3
/HF_PCLK: J10.11, J11.11, U14.5
/HOLD: J10.14, J11.14, RN3.2
/HOLDA: J10.13, J11.13, U9.5
/IOCS16: J4.2, J15.2, J16.2, J17.2, J18.2, J19.2, J20.2
/IORD: CH376.4, J1.14, J7.14, J8.14, J9.14, J12.14, J13.14, J14.14, RN2.5, U1.14, U19.9
/IOWR: CH376.2, J1.13, J7.13, J8.13, J9.13, J12.13, J13.13, J14.13, RN2.4, U1.2, U19.11
/IO_00AX: J10.7, J11.7, U13.10
/IO_00EX: CH376.6, U13.7
/IO_000X: J10.2, J11.2, U13.15
/IO_00XX: U12.15, U13.5
/IO_0XXX: U9.15, U12.5
/IO_002X: J10.3, J11.3, U13.14
/IO_004X: J10.4, J11.4, U13.13
/IO_006X: J10.5, J11.5, U13.12, U17.15
/IO_008X: J10.6, J11.6, U13.11
/IO_0060: U17.12, U19.7
/IO_0061: U1.1, U1.15, U17.11
/IRQ1: J10.1, J11.1, U19.39
/IRQ3: J1.25, J7.25, J8.25, J9.25, J12.25, J13.25, J14.25
/IRQ4: J1.24, J7.24, J8.24, J9.24, J12.24, J13.24, J14.24
/IRQ5: J1.23, J7.23, J8.23, J9.23, J12.23, J13.23, J14.23
/IRQ6: J1.22, J7.22, J8.22, J9.22, J12.22, J13.22, J14.22
/IRQ7: J1.21, J7.21, J8.21, J9.21, J12.21, J13.21, J14.21
/IRQ9: J1.4, J7.4, J8.4, J9.4, J12.4, J13.4, J14.4
/IRQ10: J4.3, J15.3, J16.3, J17.3, J18.3, J19.3, J20.3
/IRQ11: J4.4, J15.4, J16.4, J17.4, J18.4, J19.4, J20.4
/IRQ12: J4.5, J15.5, J16.5, J17.5, J18.5, J19.5, J20.5
/IRQ14: J4.7, J15.7, J16.7, J17.7, J18.7, J19.7, J20.7
/IRQ15: J4.6, J15.6, J16.6, J17.6, J18.6, J19.6, J20.6
/KBD_CLK: U16.11, U19.41
/KBD_CLK_INVERTED: U16.10, U20.1
/KBD_DATA: U19.42, U20.3
/LA17: J4.29, J15.29, J16.29, J17.29, J18.29, J19.29, J20.29
/LA18: J4.30, J15.30, J16.30, J17.30, J18.30, J19.30, J20.30
/LA19: J4.31, J15.31, J16.31, J17.31, J18.31, J19.31, J20.31
/LA20: J4.32, J15.32, J16.32, J17.32, J18.32, J19.32, J20.32
/LA21: J4.33, J15.33, J16.33, J17.33, J18.33, J19.33, J20.33
/LA22: J4.34, J15.34, J16.34, J17.34, J18.34, J19.34, J20.34
/LA23: J4.35, J15.35, J16.35, J17.35, J18.35, J19.35, J20.35
/LED_GND: D1.1, R1.1
/MASTER: J4.17, J15.17, J16.17, J17.17, J18.17, J19.17, J20.17, RN5.7
/MEMCS16: J4.1, J15.1, J16.1, J17.1, J18.1, J19.1, J20.1
/MEMR: J4.28, J15.28, J16.28, J17.28, J18.28, J19.28, J20.28, RN5.2
/MEMW: J4.27, J15.27, J16.27, J17.27, J18.27, J19.27, J20.27, RN5.3
/MRD: J1.12, J7.12, J8.12, J9.12, J12.12, J13.12, J14.12, RN2.3
/MWR: J1.11, J7.11, J8.11, J9.11, J12.11, J13.11, J14.11, RN2.2
/NC: J1.8, J7.8, J8.8, J9.8, J12.8, J13.8, J14.8
/NMI: J10.8, J11.8, U16.4
/NMI_EN: RN3.4, U2.16, U15.17, U16.1
/NMI_EN_139: U16.2, U17.1
/NMI_INPUT: U16.3, U17.4
/OSC: R3.2, R14.2, U11.12
/OSC88: J1.30, J7.30, J8.30, J9.30, J12.30, J13.30, J14.30, R14.1
/OSC88HF: R3.1, U14.11
/P61_2: U2.13, U15.14
/P61_3: U2.14, U15.15
/P61_4: U2.15, U15.16
/P61_6: U2.17, U15.18
/P61_7: U2.18, U15.19
/PCLK: R17.2, U11.2
/PCLK88: R17.1, U14.3
/PORT_0X61_CS: U15.11, U16.8
/PORT_0X61_EN: U1.4, U16.9
/PORT_61_RD: U1.12, U2.19
/POWER_GOOD: ATXPOWER1.8, R5.1
/POWER_ON: 8x8mm1.2, ATXPOWER1.16, J6.1
/RDY1: J1.41, J7.41, J8.41, J9.41, J12.41, J13.41, J14.41, R6.2, U11.4
/READY: J10.15, J11.15, U11.5
/REFRQ: J1.19, J7.19, J8.19, J9.19, J12.19, J13.19, J14.19, RN2.6
/RESET: J10.16, J11.16, R5.2, SW1.1, U11.11, U19.5
/RESOUT: J1.2, J7.2, J8.2, J9.2, J12.2, J13.2, J14.2, U11.10
/SBHE: J4.36, J15.36, J16.36, J17.36, J18.36, J19.36, J20.36
/SPK_EN: U2.12, U15.13, U16.5
/SPK_EN_: U16.6, U117.15
/SPK_GO: J10.10, J11.10, U2.11, U15.12
/SPK_OUT: J10.9, J11.9, U117.14
/SPK_PIN: U3.2, U117.12
/SPK_PIN_O: J3.1, U3.1
/T0: J2.5, R8.2, U19.2, U20.2
/T1: J2.1, R9.2, U19.43, U20.4
/TC: J1.27, J7.27, J8.27, J9.27, J12.27, J13.27, J14.27, R13.2
/X1_8284: R4.1, U11.17, Y2.2
/X2_8284: R2.1, U11.16, Y2.1

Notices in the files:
Kicad/512K ISA/512k.kicad_pcb:
Copyright (C) 2022 EMM
Kicad/8086 ISA ver2/8086.kicad_pcb:
Copyright (C) 2025 EMM
